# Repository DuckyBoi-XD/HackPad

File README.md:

# DuckyDK Pad 7K2R

## Features
- 7 Switches including 1 2.00u and 6 1.00u
- 2 Rotary knobs 
- 7 LEDs as backlight for switches

## Specifications
BOM:
- 7x Cherry MX Switches
- 7x Blank DSA 1.00u keycaps
- 7x SK6812 Neopixels
- 2x EC11 Rotary Encoder - RotaryEncoder_Switch
- 2x Rotary knob
- 1x XIAO RP2040
- 4x M3x5mx4mm heatset insert
- 4x M3x16mm screws
(Sadly, no stabilisers or 2.00u keycap :c)

## Inspiration
This is my first time using electrical engineering to create a working macropad, which I have always wanted to try to make. I've always been interested in electrical engineering (I've made a simple lamp post model), and I wanted to continue my hobby. I use the Hackpad guide and people on Slack to help me understand and get used to the software. I wanted to used 8 keys and 2 Rotary Encoder, but I wasn't able to use 10 inputs with the Xiao RP2040 for it, so I learnt how to use a matrix and use 7 Keys and 2 Rotary encoder for my project. This is also why it's called the 7K2R - 7 Key and 2 Rotary encoders, (The DuckyDk refers to my username DuckyBoi_XD and DK for Drum Kit or Duck again)

## Firmware Overview  

The firmware of this macropad was made by QinCai and contains:

- 7 Keys which linked to macro key which can be changed
- 2 Rotary encoders,
  - 1 adjusting volume and a switch muting the volume
  - 1 adjusting LEDs brightness and a off button
- 7 LEDs under switches which we have as a single colour

### Schematics

### PCB

### Case

## Credit
I'd like to give credit to everyone who has helped in this project,

- [@Person20020 (Koji)](https://hackclub.slack.com/team/U07QNKS5SKA), for answering almost every question I had while making the pad, and pretty much telling me what to do because I had no clue. I'm thankful that Person20020 is an expert in Kicad and Fusion because without them, I wouldn't have been able to finish
- [@QinCai](https://hackclub.slack.com/team/U07BNRCEARM), for being my irl friend, introducing me to Hackclub, supporting me, giving me tips, helping with this repo, and making my firmware (I can't code)
- [@StrawberryPuding](https://hackclub.slack.com/team/U08290982KU), for answering my question when Person wasn't online and helping me understand Rotary encoders
- [@alexren](https://hackclub.slack.com/team/U06PR6B8D37) and [@acon](https://hackclub.slack.com/team/U04KEK4TS72), for being amazing organisers and often helping people like me with details and questions
- The entire Slack community, for answers to all my strange questions about Hackclub, Hackpad and electrical engineering in general

## Extra Information

The Fusion model contains a derived version of my case, which contains my bottom case and top case as well as the PCB export. I have the main version plus the models I derived from it, but it contains switches, stabilisers, rotary encoders and Xiao MCU models. I read the guide, and it says just to add a single file for the case so I did. If the person reviewing thing project needs the main file for the case, try to message me.

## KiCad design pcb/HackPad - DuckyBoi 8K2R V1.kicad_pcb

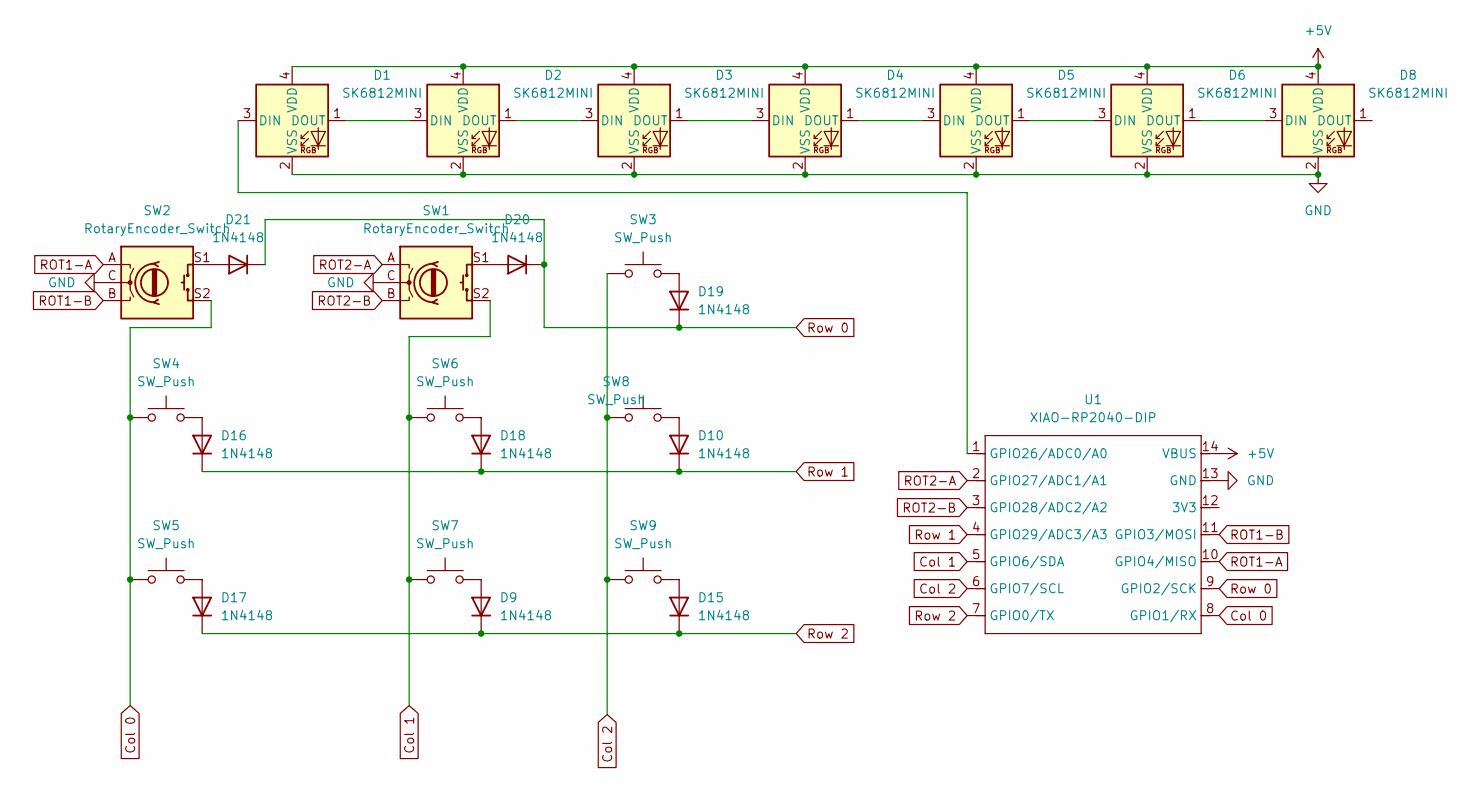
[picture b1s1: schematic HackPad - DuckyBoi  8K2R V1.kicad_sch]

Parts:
D1, D2, D3, D4, D5, D6, D8: SK6812MINI; LED_SK6812MINI
D9, D10, D15, D16, D17, D18, D19, D20, D21: 1N4148; D_DO-35_SOD27_P7.62mm_Horizontal
SW1, SW2: RotaryEncoder_Switch; RotaryEncoder_Alps_EC11E-Switch_Vertical_H20mm
SW3: SW_Push; SW_Cherry_MX_2.00u_Vertical_PCB
SW4, SW5, SW6, SW7, SW8, SW9: SW_Push; SW_Cherry_MX_1.00u_PCB
U1: XIAO-RP2040-DIP

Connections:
+5V: D1.4 (VDD), D2.4 (VDD), D3.4 (VDD), D4.4 (VDD), D5.4 (VDD), D6.4 (VDD), D8.4 (VDD), U1.14 (VBUS)
Col 0: SW2.S2, SW4.1, SW5.1, U1.8 (GPIO1/RX)
Col 1: SW1.S2, SW6.1, SW7.1, U1.5 (GPIO6/SDA)
Col 2: SW3.1, SW8.1, SW9.1, U1.6 (GPIO7/SCL)
GND: D1.2 (VSS), D2.2 (VSS), D3.2 (VSS), D4.2 (VSS), D5.2 (VSS), D6.2 (VSS), D8.2 (VSS), SW1.C, SW2.C, U1.13 (GND)
unnamed: D1.3 (DIN), U1.1 (GPIO26/ADC0/A0)
unnamed: D1.1 (DOUT), D2.3 (DIN)
unnamed: D2.1 (DOUT), D3.3 (DIN)
unnamed: D3.1 (DOUT), D4.3 (DIN)
unnamed: D4.1 (DOUT), D5.3 (DIN)
unnamed: D5.1 (DOUT), D6.3 (DIN)
unnamed: D6.1 (DOUT), D8.3 (DIN)
unnamed: D9.2 (A), SW7.2
unnamed: D10.2 (A), SW8.2
unnamed: D15.2 (A), SW9.2
unnamed: D16.2 (A), SW4.2
unnamed: D17.2 (A), SW5.2
unnamed: D18.2 (A), SW6.2
unnamed: D19.2 (A), SW3.2
unnamed: D20.2 (A), SW1.S1
unnamed: D21.2 (A), SW2.S1
ROT1-A: SW2.A, U1.10 (GPIO4/MISO)
ROT1-B: SW2.B, U1.11 (GPIO3/MOSI)
ROT2-A: SW1.A, U1.2 (GPIO27/ADC1/A1)
ROT2-B: SW1.B, U1.3 (GPIO28/ADC2/A2)
Row 0: D19.1 (K), D20.1 (K), D21.1 (K), U1.9 (GPIO2/SCK)
Row 1: D10.1 (K), D16.1 (K), D18.1 (K), U1.4 (GPIO29/ADC3/A3)
Row 2: D9.1 (K), D15.1 (K), D17.1 (K), U1.7 (GPIO0/TX)

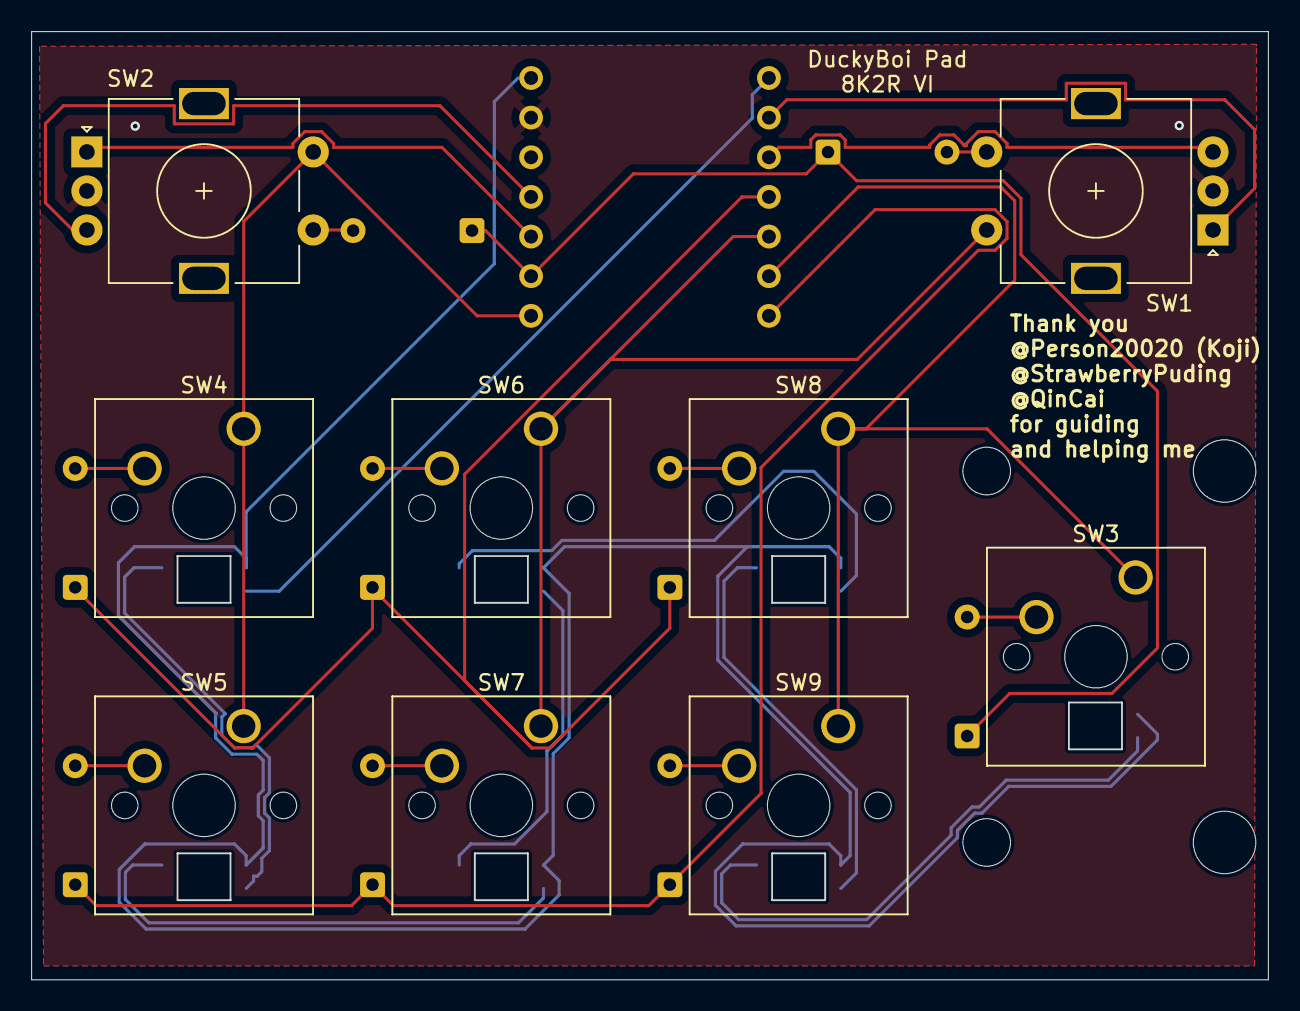
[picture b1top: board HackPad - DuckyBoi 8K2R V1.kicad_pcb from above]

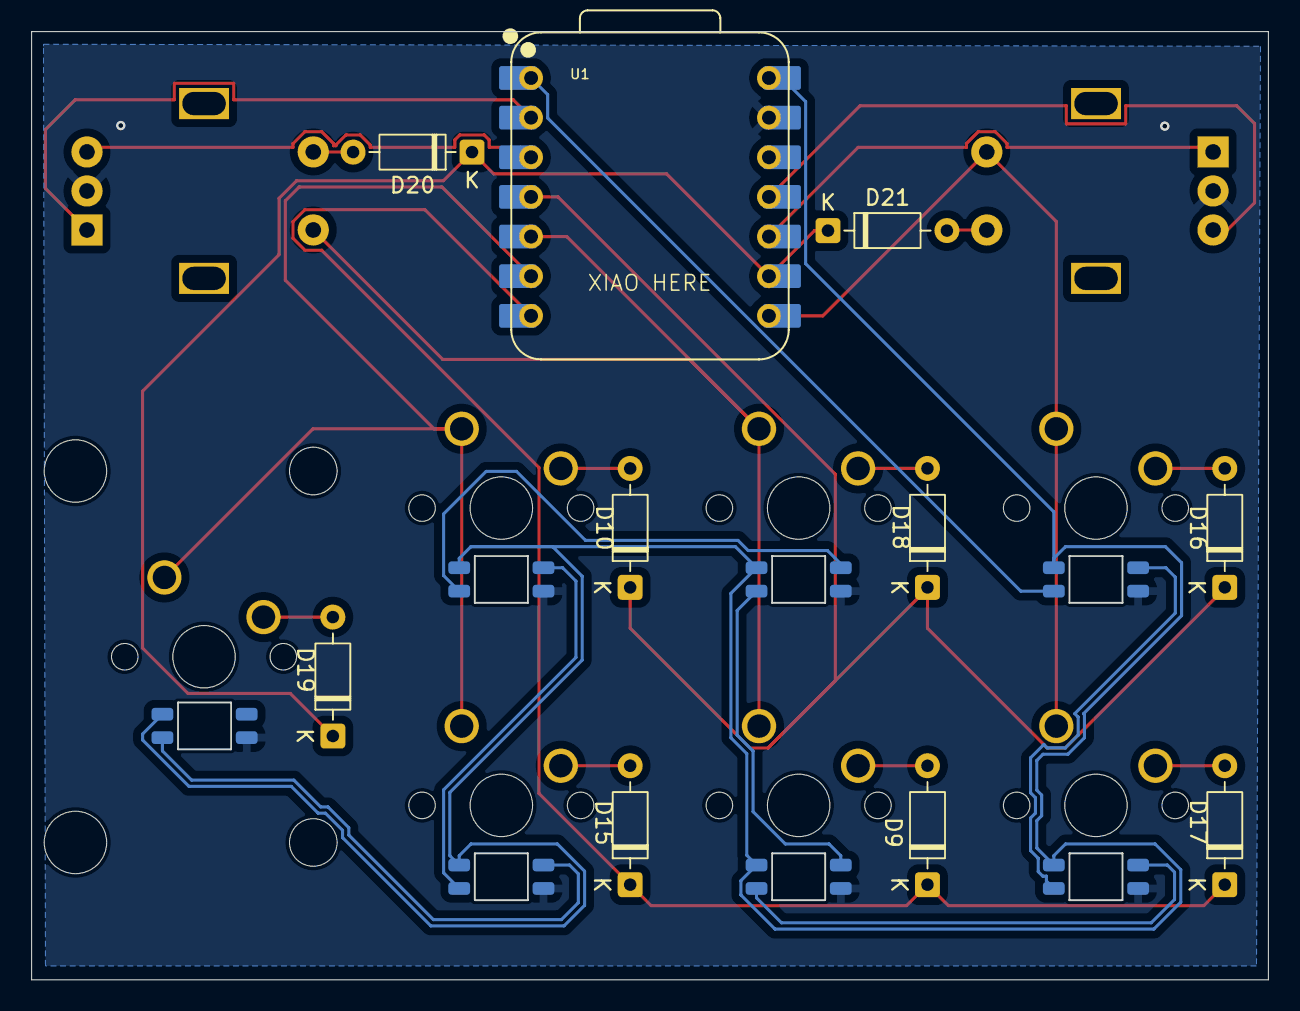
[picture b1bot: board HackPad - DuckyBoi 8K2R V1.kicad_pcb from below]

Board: 2 copper layers, 79.2 x 60.7 mm, 26 parts (17 on the bottom side), 28 nets.

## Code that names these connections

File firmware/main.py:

################################################################################
# VERY USEFUL: https://github.com/KMKfw/kmk_firmware/tree/main/docs/en         #
################################################################################

import board
import busio
from digitalio import DigitalInOut, Direction, Pull

from kmk.kmk_keyboard import KMKKeyboard
from kmk.keys import KC
from kmk.scanners import DiodeOrientation
from kmk.extensions.media_keys import MediaKeys
from kmk.modules.macros import Macros
from kmk.modules.encoder import EncoderHandler

# Initialise keyboard
keyboard = KMKKeyboard()

# Configure diode orientation - 1N4148 diodes
keyboard.diode_orientation = DiodeOrientation.COL2ROW

# Matrix pins
# ROW pins are connected to GPIO0/TX (ROW 2), GPIO1/RX (ROW 1), and GPIO2/SCK (ROW 0)
keyboard.row_pins = (board.SCK, board.RX, board.TX)  # ROW 0, ROW 1, ROW 2

# COL pins are connected to GPIO6/SDA (COL 2), GPIO7/SCL (COL 1), and GPIO29/ADC3 (COL 0)
keyboard.col_pins = (board.A3, board.SCL, board.SDA)  # COL 0, COL 1, COL 2

# Initialise modules
macros = Macros()
media_keys = MediaKeys()

# Keep the RGB LED pin allocation (GPIO26/ADC0) but don't initialise the RGB module
rgb_pin = board.A0  # reserves the pin

# Initialise encoder handler for two rotary encoders
encoder_handler = EncoderHandler()

# Configure encoder pins:
# Encoder 1: ROT1-A (GPIO27/ADC1), ROT1-B (GPIO28/ADC2)
# Encoder 2: ROT2-A (GPIO4/MISO), ROT2-B (GPIO3/MOSI)
encoder_handler.pins = (
    (board.A1, board.A2, KC.MUTE),  # Encoder 1 (SW2) - Volume control with mute
    (board.MISO, board.MOSI, KC.MUTE)  # Encoder 2 (SW1) - Brightness control with mute (idk what to change it to)
)

# Common macros
COPY = KC.LGUI(KC.C)  # Command+C for macOS
PASTE = KC.LGUI(KC.V)  # Command+V ''
CUT = KC.LGUI(KC.X)    # Command+X ''
UNDO = KC.LGUI(KC.Z)   # Command+Z ''
SAVE = KC.LGUI(KC.S)   # Command+S ''
SPOTLIGHT = KC.LGUI(KC.SPACE)  # Command+Space for Spotlight
MISSION = KC.LGUI(KC.UP)  # Command+Up for Mission Control

# Add extensions and modules to the keyboard
keyboard.extensions.append(media_keys)
keyboard.modules.append(macros)
keyboard.modules.append(encoder_handler)

# Define keyboard layout - single layer (for now) with most useful functions
keyboard.keymap = [
    [
        # ROW 0
        SAVE,            SPOTLIGHT,   MISSION,
        # ROW 1
        COPY,            PASTE,       CUT,
        # ROW 2
        KC.LGUI(KC.TAB), UNDO,        KC.ESC
    ]
]

# Configure encoders
# Encoder 1: Volume control with mute
# Encoder 2: Brightness control with mute (idk what to change it to)
encoder_handler.map = (
    ((KC.VOLD, KC.VOLU, KC.MUTE), (KC.BRID, KC.BRIU, KC.MUTE)),
)

if __name__ == "__main__":
    keyboard.go()

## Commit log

2025-05-23 Create LICENSE
2025-05-24 oops nvm we are using kmk, not qmk...
2025-05-24 move main.py to a specific (kmk) directory
2025-05-24 add the file back
2025-05-24 update firmware
2025-05-25 Additon of files of pcb schematics and pro kicad
2025-05-25 test
2025-05-26 update gitignore
2025-05-26 repo cleanup
2025-05-26 add back the project file
2025-05-26 Update firmware to add support for RGB neopixels
2025-05-26 actually there are 7 neopixels
2025-05-27 Update cusz stupid clearnace level and errors and warnings
2025-06-01 update, changed name, past update, revamped xiao location and wiring
2025-06-01 update, changed file name
2025-06-01 update, changed file name fix
2025-06-01 Fixed Sharp corners on pcb
2025-06-01 Fixed main name AGAIN
2025-06-01 Create production
2025-06-01 Create Production folder
2025-06-01 Added cad files to show case the case
2025-06-01 Re added pcb files - Broken git terminal
2025-06-01 gerbers files pcb added
2025-06-01 Added cad view model + pcb
2025-06-01 Added top and bottom production case parts
2025-06-01 Change README.md
2025-06-01 Create README.md started writing
2025-06-01 Update README.md Finished it
2025-06-01 Update README.md added extra info
2025-06-01 Update README.md added titles for overview
2025-06-01 add firmware to prod
2025-06-01 Update README.md remove most overviews
2025-06-01 operation deletion
2025-06-01 Update README.md alex credit
2025-06-01 operation deletion (v2)
2025-06-01 Update README.md positioning
2025-06-01 Update README.md fixed sch
2025-06-01 actually 7 keys :))
2025-06-01 Update README.md added firmware oveeview
2025-06-02 Update README.md firmware led
2025-06-02 Update README.md fixed bom
2025-06-02 Update README.md firmware
2025-06-02 add feature & bug fix
2025-06-02 copy firmware to prod
2025-06-02 readme init
2025-06-02 spelling mistakes :|
2025-06-02 add license
2025-06-02 Update LICENSE
2025-06-02 license
2025-06-02 Update pins
2025-06-02 Update README.md firmware fix
